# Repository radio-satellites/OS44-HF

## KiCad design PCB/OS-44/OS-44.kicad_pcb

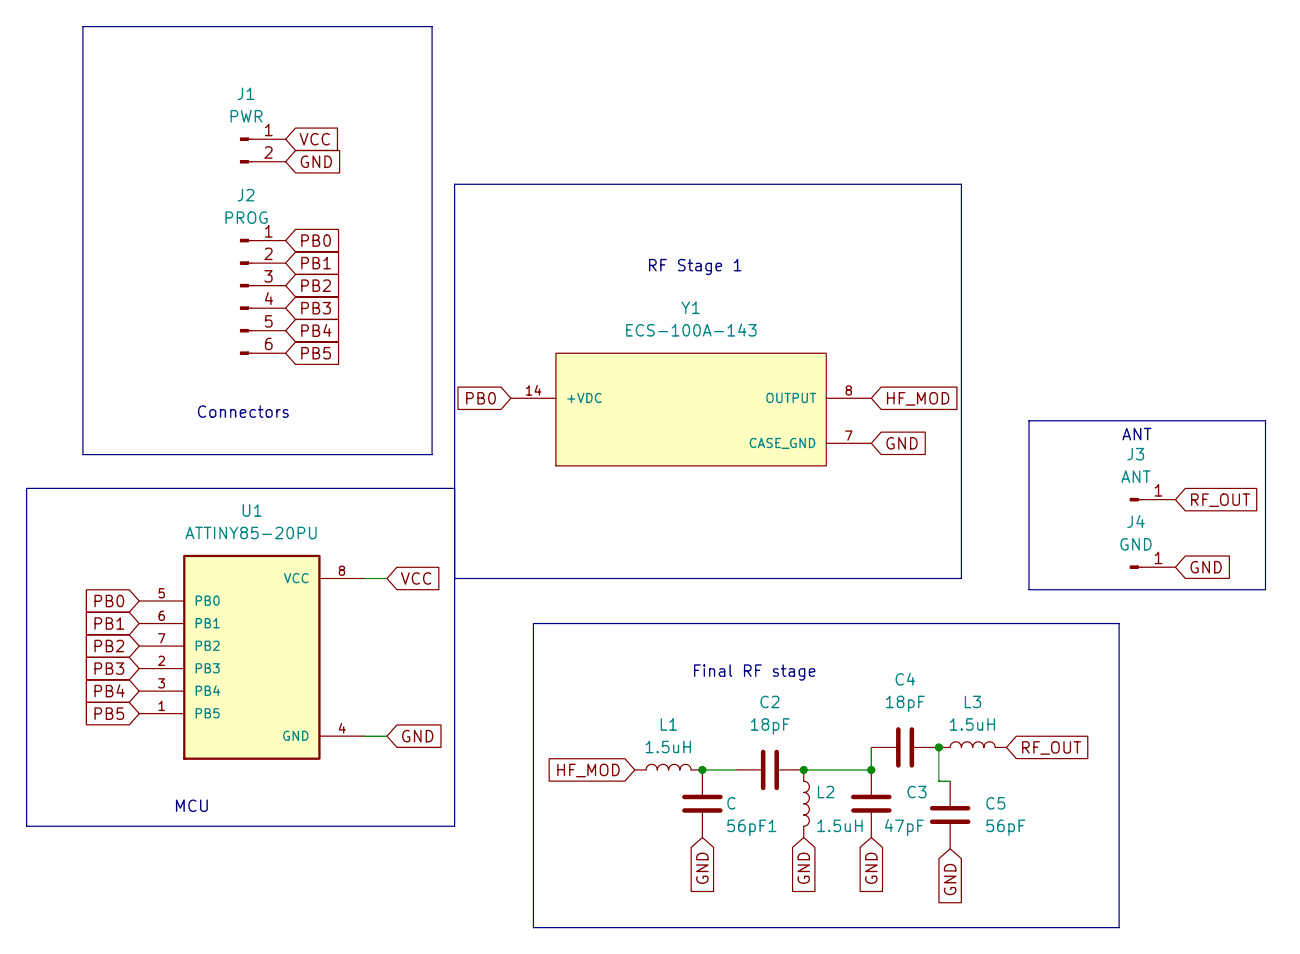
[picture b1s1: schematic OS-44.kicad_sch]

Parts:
56pF1: C; C_1210_3225Metric_Pad1.33x2.70mm_HandSolder
C2, C4: 18pF; C_1206_3216Metric_Pad1.33x1.80mm_HandSolder
C3: 47pF; C_1206_3216Metric_Pad1.33x1.80mm_HandSolder
C5: 56pF; C_1210_3225Metric_Pad1.33x2.70mm_HandSolder
J1: PWR; PinSocket_1x02_P2.54mm_Vertical
J2: PROG; PinSocket_1x06_P2.54mm_Vertical
J3: ANT; TestPoint_THTPad_D2.5mm_Drill1.2mm
J4: GND; TestPoint_THTPad_D2.5mm_Drill1.2mm
L1, L2, L3: 1.5uH; L_0805_2012Metric_Pad1.15x1.40mm_HandSolder
U1: ATTINY85-20PU; ATTINY85
Y1: ECS-100A-143; OSC_ECS-100A-143

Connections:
GND: 56pF1.2, C3.2, C5.2, J1.2, J4.1, L2.2, U1.4 (GND), Y1.7 (CASE_GND); also elsewhere on the board
HF_MOD: L1.1, Y1.8 (OUTPUT)
unnamed 2: 56pF1.1, C2.1, L1.2; also elsewhere on the board
unnamed: C2.2, C3.1, C4.1, L2.1
unnamed: C4.2, C5.1, L3.1
PB0: J2.1, U1.5 (PB0), Y1.14 (+VDC)
PB1: J2.2, U1.6 (PB1)
PB2: J2.3, U1.7 (PB2)
PB3: J2.4, U1.2 (PB3)
PB4: J2.5, U1.3 (PB4)
PB5: J2.6, U1.1 (PB5)
RF_OUT: J3.1, L3.2
VCC: J1.1, U1.8 (VCC)

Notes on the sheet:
ANT
RF Stage 1
MCU
Connectors
Final RF stage

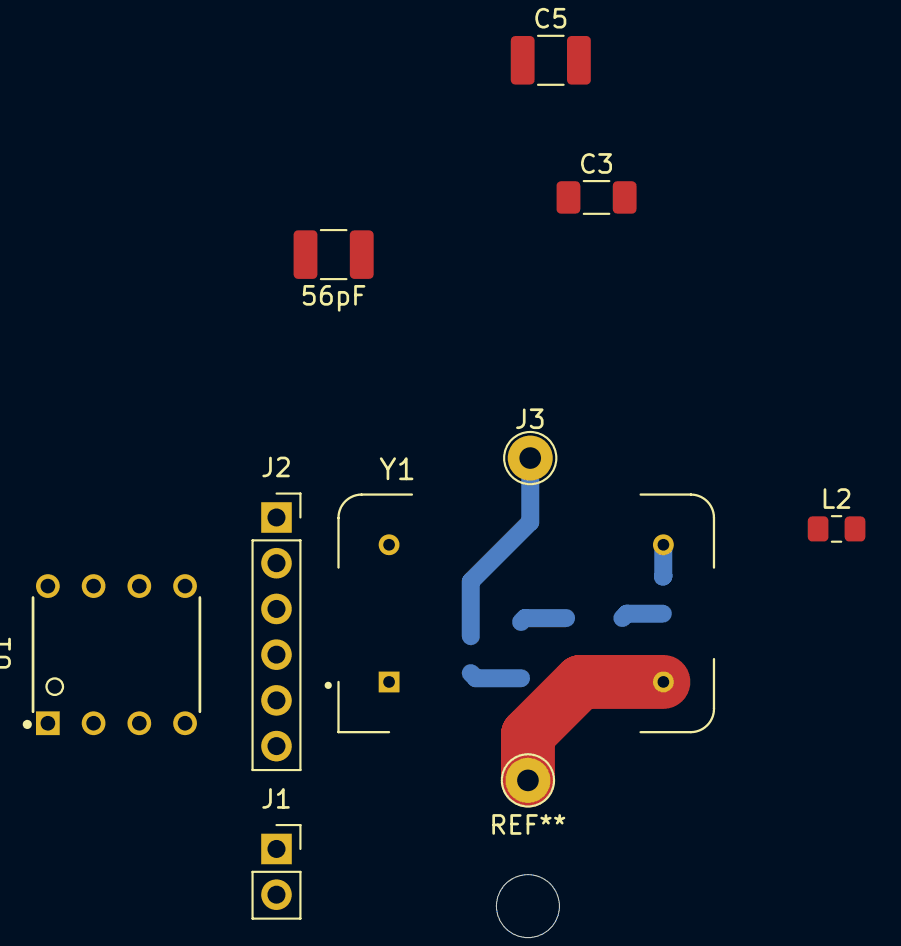
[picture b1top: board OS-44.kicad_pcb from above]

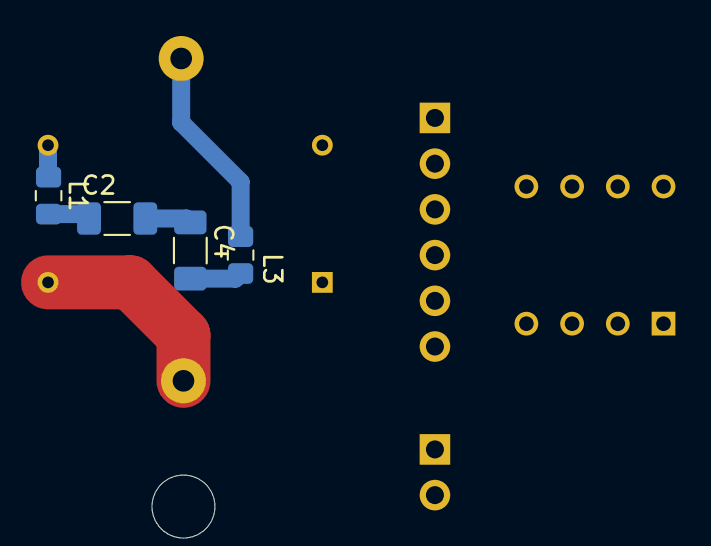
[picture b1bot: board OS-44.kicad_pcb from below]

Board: 2 copper layers, 14 parts (4 on the bottom side), 13 nets.

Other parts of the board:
56pF: C; C_1210_3225Metric_Pad1.33x2.70mm_HandSolder

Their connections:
GND: 56pF.2; also elsewhere on the board
unnamed 2: 56pF.1; also elsewhere on the board
